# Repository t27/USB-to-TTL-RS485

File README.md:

#USB to TTL RS485

This board convert USB to RS485 and TTL on the same board. Thereby allowing the control of both RS485 and TTL based motors at one time. 

It can be used to control Robotis TTL and RS485 based motors at one time. Headers for both TTL and RS485 are provided on board. 

The connection type can be configured using an onboard 3 way jumper. If all three pads are shorted, then both TTL and TS485 will function.

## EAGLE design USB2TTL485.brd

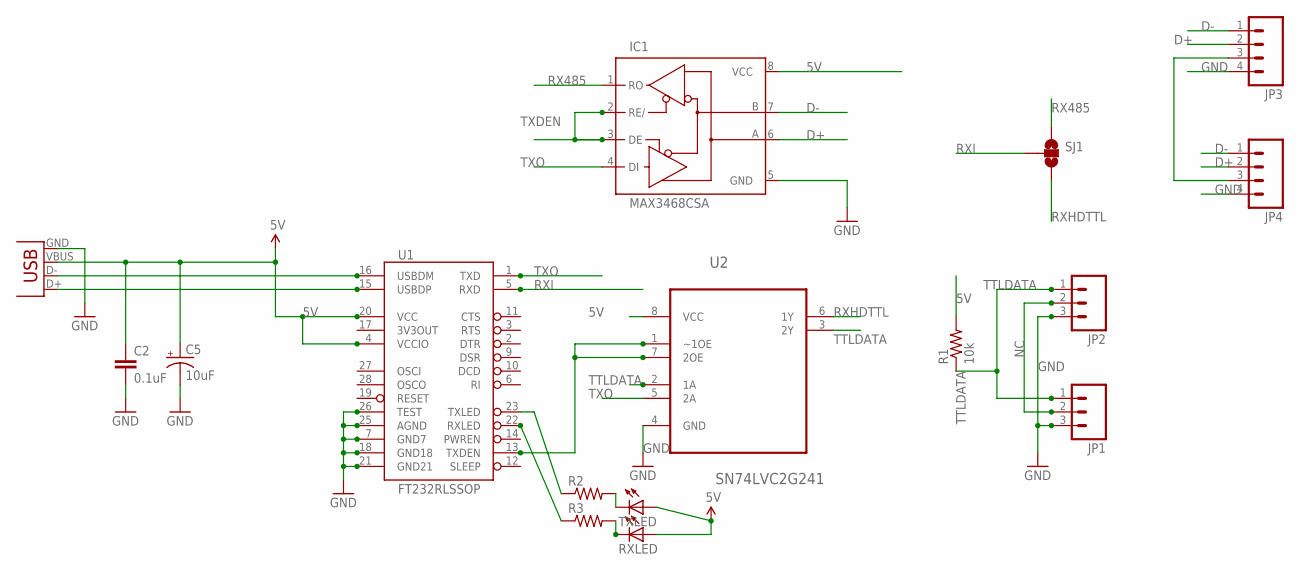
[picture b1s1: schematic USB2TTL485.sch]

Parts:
C2: 0.1uF; 0402-CAP
C5: 10uF; EIA3216
IC1: MAX3468CSA; SO08
JP1, JP2: M03LOCK_LONGPADS; 1X03_LOCK_LONGPADS
JP3, JP4: M04LOCK_LONGPADS; 1X04_LOCK_LONGPADS
R1: 10k; 0603-RES
R2, R3: RESISTOR0603-RES; 0603-RES
RXLED: LED0603; LED-0603
SJ1: SOLDERJUMPER_2WAYT; SJ_2
TXLED: LED0603; LED-0603
U1: FT232RLSSOP; SSOP28DB
U2: SN74LVC2G241; SOP65P400X130-8N
X2: USB-SMD-NS; USB-MINIB-NOSTOP

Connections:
5V: C2.1, C5.A (+), IC1.8 (VCC), R1.2, RXLED.A, TXLED.A, U1.4 (VCCIO), U1.20 (VCC), U2.8 (VCC), X2.VBUS
D+: IC1.6 (A), JP3.2, JP4.2
D-: IC1.7 (B), JP3.1, JP4.1
GND: C2.2, C5.C (-), IC1.5 (GND), JP1.3, JP2.3, JP3.4, JP4.4, U1.7 (GND7), U1.18 (GND18), U1.21 (GND21), U1.25 (AGND), U1.26 (TEST), U2.4 (GND), X2.GND
unnamed: R2.2, TXLED.C
unnamed: R2.1, U1.23 (TXLED)
unnamed: R3.1, U1.22 (RXLED)
unnamed: JP3.3, JP4.3
unnamed: R3.2, RXLED.C
NC: JP1.2, JP2.2
RX485: IC1.1 (RO), SJ1.1
RXHDTTL: SJ1.3, U2.6 (1Y)
RXI: SJ1.2, U1.5 (RXD)
TTLDATA: JP1.1, JP2.1, R1.1, U2.2 (1A), U2.3 (2Y)
TXDEN: IC1.2 (RE/), IC1.3 (DE), U1.13 (TXDEN), U2.1 (~1OE), U2.7 (2OE)
TXO: IC1.4 (DI), U1.1 (TXD), U2.5 (2A)
USB_D+: U1.15 (USBDP), X2.D+
USB_D-: U1.16 (USBDM), X2.D-

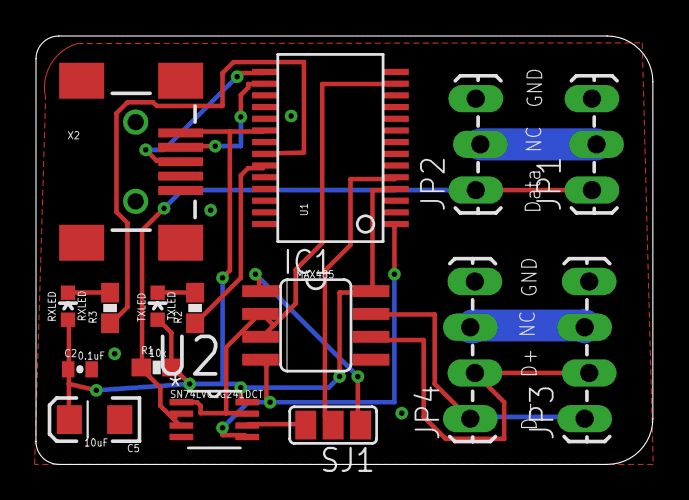
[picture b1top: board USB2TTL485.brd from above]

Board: 2 copper layers, 34.3 x 23.8 mm, 16 parts (0 on the bottom side), 18 nets.

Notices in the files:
parts and their libraries:
SparkFun-Connectors: Licensing: CC v3.0 Share-Alike You are welcome to use this library for commercial purposes.
